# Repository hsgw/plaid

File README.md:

Plaid-C
=================

The 4x12 ortholinear keyboard kit made by through hole components only.

This is an updated version modified to use USB-C instead of Mini USB by piit79.

Atmega328p with VUSB on [QMK firmware](https://github.com/qmk/qmk_firmware).

[Build guide and bom is here](./doc)
[ビルドガイドとパーツリストはこちら](./doc)

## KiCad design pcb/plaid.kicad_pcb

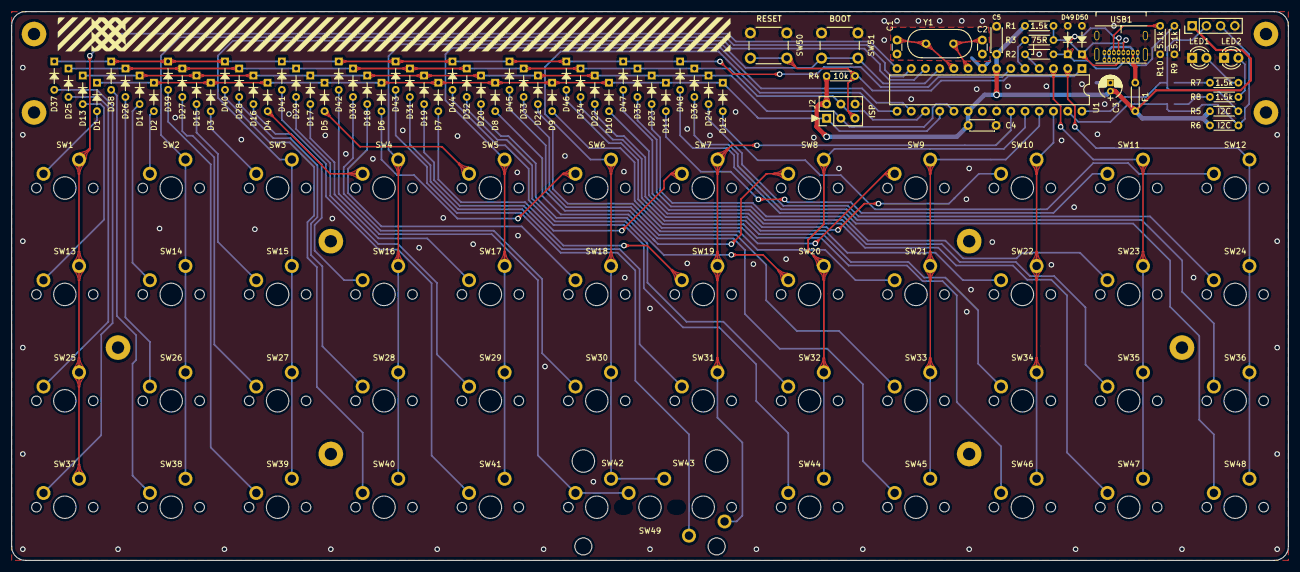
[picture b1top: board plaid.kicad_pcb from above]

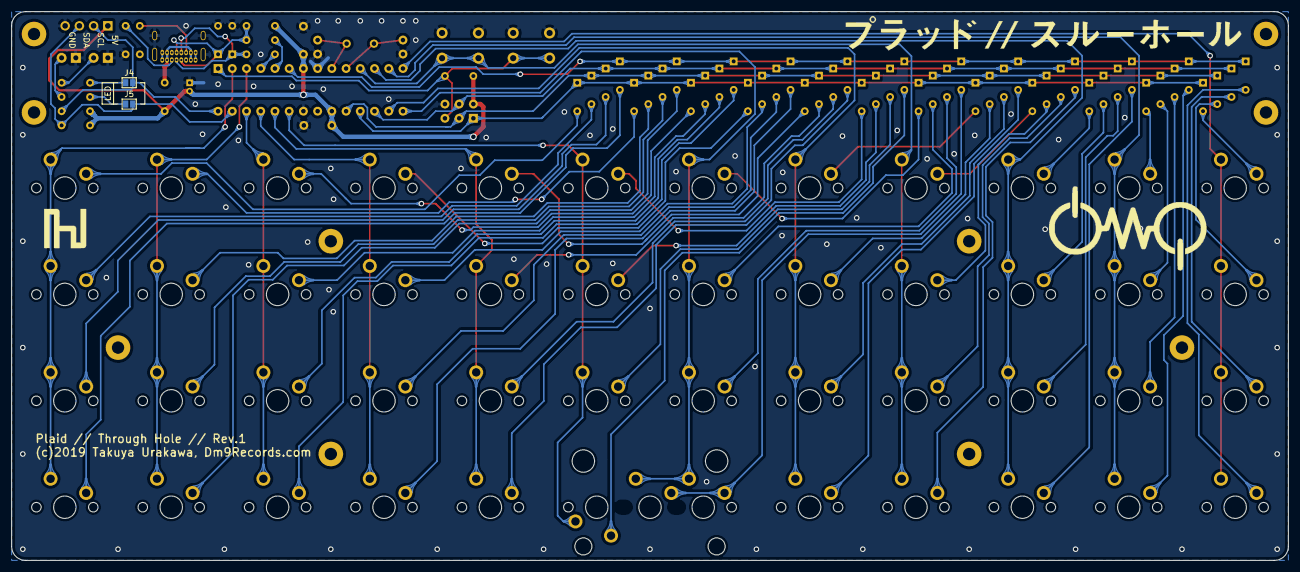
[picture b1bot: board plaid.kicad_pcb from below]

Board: 2 copper layers, 228.0 x 98.0 mm, 136 parts (2 on the bottom side), 82 nets.

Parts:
C1, C2: 20p; C_Disc_D3.0mm_W1.6mm_P2.50mm
C3: 4.7u; CP_Radial_D4.0mm_P1.50mm
C4, C5: 100n; C_Disc_D4.3mm_W1.9mm_P5.00mm
D1, D2, D3, D4, D5, D6, D7, D8, D9, D10, D11, D12, D13, D14, D15, D16, D17, D18, D19, D20, D21, D22, D23, D24, D25, D26, D27, D28, D29, D30, D31, D32, D33, D34, D35, D36, D37, D38, D39, D40, D41, D42, D43, D44, D45, D46, D47, D48: 1N4148; D_DO-35_SOD27_P5.08mm_Horizontal
D49, D50: 3.6V; D_DO-35_SOD27_P5.08mm_Horizontal
F1: 100mA; polyfuse_5.1mm
H1, H2, H3, H4, H5, H6, H7, H8, H9, H10: M2; MountingHole_2.2mm_M2_Pad
J2: AVR_ISP_6; Pin_Header_Straight_2x03_Pitch2.54mm
J3: Conn_01x04; Pin_Header_Straight_1x04_Pitch2.54mm
J4, J5: GS2
LED1: RED; LED_D3.0mm
LED2: GREEN; LED_D3.0mm
R1, R7, R8: 1.5k; R_Axial_DIN0204_L3.6mm_D1.6mm_P5.08mm_Horizontal
R2, R3: 75R; R_Axial_DIN0204_L3.6mm_D1.6mm_P5.08mm_Horizontal
R4: 10k; R_Axial_DIN0204_L3.6mm_D1.6mm_P5.08mm_Horizontal
R5, R6: I2C; R_Axial_DIN0204_L3.6mm_D1.6mm_P5.08mm_Horizontal
R9, R10: 5.1k; R_Axial_DIN0204_L3.6mm_D1.6mm_P5.08mm_Horizontal
SW1, SW2, SW3, SW4, SW5, SW6, SW7, SW8, SW9, SW10, SW11, SW12, SW13, SW14, SW15, SW16, SW17, SW18, SW19, SW20, SW21, SW22, SW23, SW24, SW25, SW26, SW27, SW28, SW29, SW30, SW31, SW32, SW33, SW34, SW35, SW36, SW37, SW38, SW39, SW40, SW41, SW42, SW43, SW44, SW45, SW46, SW47, SW48: SW_Push; SW_Cherry_MX1A_1.00u_PCB
SW49: SW_Push; SW_Cherry_MX1A_2.0U_PCB_universal_center
SW50: RESET; SW_PUSH_6mm
SW51: BOOT; SW_PUSH_6mm
U1: ATMEGA328-PU; DIP-28_W7.62mm
USB1: USB_C_GCT_USB4085-Type-C; USB_C_GCT_USB4085
Y1: 16MHz; Crystal_HC49-4H_Vertical

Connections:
+5V: C3.1, C4.1, C5.1, F1.2, J2.2, J3.1, R1.2, R4.1, R5.1, R6.1, U1.7, U1.20
/COL0: SW1.2, SW13.2, SW25.2, SW37.2, U1.14
/COL1: SW2.2, SW14.2, SW26.2, SW38.2, U1.13
/COL2: SW3.2, SW15.2, SW27.2, SW39.2, U1.12
/COL3: SW4.2, SW16.2, SW28.2, SW40.2, SW51.1, U1.11
/COL4: SW5.2, SW17.2, SW29.2, SW41.2, U1.16
/COL5: SW6.2, SW18.2, SW30.2, SW42.2, SW49.2, U1.15
/COL6: SW7.2, SW19.2, SW31.2, SW43.1, U1.23
/COL7: SW8.2, SW20.2, SW32.2, SW44.2, U1.24
/COL8: SW9.2, SW21.2, SW33.2, SW45.2, U1.25
/COL9: SW10.2, SW22.2, SW34.2, SW46.2, U1.26
/COL10: SW11.2, SW23.2, SW35.2, SW47.2, U1.3
/COL11: SW12.2, SW24.2, SW36.2, SW48.2, U1.2
/RESET: J2.5, R4.2, SW50.1, U1.1
/ROW0: D1.1, D2.1, D3.1, D4.1, D5.1, D6.1, D7.1, D8.1, D9.1, D10.1, D11.1, D12.1, J2.1, U1.18
/ROW1: D13.1, D14.1, D15.1, D16.1, D17.1, D18.1, D19.1, D20.1, D21.1, D22.1, D23.1, D24.1, J2.3, U1.19
/ROW2: D25.1, D26.1, D27.1, D28.1, D29.1, D30.1, D31.1, D32.1, D33.1, D34.1, D35.1, D36.1, J2.4, U1.17
/ROW3: D37.1, D38.1, D39.1, D40.1, D41.1, D42.1, D43.1, D44.1, D45.1, D46.1, D47.1, D48.1, U1.6
/USB_D+: R2.1, U1.4
/USB_D-: R3.1, U1.5
/i2c_SCL: J3.2, J4.2, R5.2, U1.28
/i2c_SDA: J3.3, J5.2, R6.2, U1.27
GND: C1.2, C2.2, C3.2, C4.2, C5.2, D49.2, D50.2, J2.6, J3.4, LED1.1, LED2.1, R9.1, R10.1, SW50.2, SW51.2, U1.8, U1.22, USB1.A1, USB1.A12, USB1.B1, USB1.B12, USB1.S1
unnamed: C1.1, U1.10, Y1.2
unnamed: C2.1, U1.9, Y1.1
unnamed: D1.2, SW1.1
unnamed: D2.2, SW2.1
unnamed: D3.2, SW3.1
unnamed: D4.2, SW4.1
unnamed: D5.2, SW5.1
unnamed: D6.2, SW6.1
unnamed: D7.2, SW7.1
unnamed: D8.2, SW8.1
unnamed: D9.2, SW9.1
unnamed: D10.2, SW10.1
unnamed: D11.2, SW11.1
unnamed: D12.2, SW12.1
unnamed: D13.2, SW13.1
unnamed: D14.2, SW14.1
unnamed: D15.2, SW15.1
unnamed: D16.2, SW16.1
unnamed: D17.2, SW17.1
unnamed: D18.2, SW18.1
unnamed: D19.2, SW19.1
unnamed: D20.2, SW20.1
unnamed: D21.2, SW21.1
unnamed: D22.2, SW22.1
unnamed: D23.2, SW23.1
unnamed: D24.2, SW24.1
unnamed: D25.2, SW25.1
unnamed: D26.2, SW26.1
unnamed: D27.2, SW27.1
unnamed: D28.2, SW28.1
unnamed: D29.2, SW29.1
unnamed: D30.2, SW30.1
unnamed: D31.2, SW31.1
unnamed: D32.2, SW32.1
unnamed: D33.2, SW33.1
unnamed: D34.2, SW34.1
unnamed: D35.2, SW35.1
unnamed: D36.2, SW36.1
unnamed: D37.2, SW37.1
unnamed: D38.2, SW38.1
unnamed: D39.2, SW39.1
unnamed: D40.2, SW40.1
unnamed: D41.2, SW41.1
unnamed: D42.2, SW42.1, SW49.1
unnamed: D43.2, SW43.2
unnamed: D44.2, SW44.1
unnamed: D45.2, SW45.1
unnamed: D46.2, SW46.1
unnamed: D47.2, SW47.1
unnamed: D48.2, SW48.1
unnamed: D49.1, R2.2, USB1.A6, USB1.B6
unnamed: D50.1, R1.1, R3.2, USB1.A7, USB1.B7
unnamed: F1.1, USB1.A4, USB1.A9, USB1.B4, USB1.B9
unnamed: J4.1, R7.1
unnamed: J5.1, R8.1
unnamed: LED1.2, R7.2
unnamed: LED2.2, R8.2
unnamed: R9.2, USB1.A5
unnamed: R10.2, USB1.B5

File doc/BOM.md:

# BOM 
## Included in Plaid kit
|                                   | Ref         | Qty | Value               | Description                                 |
|-----------------------------------|-------------|-----|---------------------|---------------------------------------------|
| ![22pF](./img/parts/P1020154.JPG) | C1, C2      | 2   | 22p                 | Multi layer ceramic capacitor (2.5mm pitch) |
| ![4.7uF](./img/parts/P1020157.JPG)              | C3          | 1   | 4.7u                | Electrolytic capacitor (1.5mm pitch)        |
| ![100nF](./img/parts/P1020155.JPG)              | C4, C5      | 2   | 100n                | Multi layer ceramic capacitor (5mm pitch)   |
| ![1N4148](./img/parts/P1020138.JPG)              | D1-48       | 48  | 1N4148              | General-purpose diode (DO-35)               |
| ![3.6V](./img/parts/P1020151.JPG)              | D49, D50    | 2   | 3.6V                | 3.6V Schottky diode (DO-35)                 |
| ![fuse](./img/parts/P1020156.JPG)              | F1          | 1   | 100mA               | Resettable fuse (5mm pitch)                 |
| ![USB](./img/parts/P1020147.JPG)              | J1          | 1   | USB MINI-B          | USB miniB connector                         |
| ![2x3](./img/parts/P1020158.JPG)              | J2          | 1   | 02x03               | AVR ISP pin header                          |
| ![LED](./img/parts/P1020159.JPG)              | LED1,2      | 2   | RED, GREEN              | 3mm LED                                     |
| ![1.5k](./img/parts/P1020161.JPG)              | R1, R7, R8  | 3   | 1.5k                | 1/6W resistor                               |
| ![75R](./img/parts/P1020160.JPG)              | R2, R3      | 2   | 75R                 | 1/6W resistor                               |
| ![10k](./img/parts/P1020162.JPG)              | R4          | 1   | 10k                 | 1/6W resistor                               |
| ![](./img/parts/P1020153.JPG)              | SW50, SW51     | 2   | RESET, BOOT         | 6mm tactile switch                          |
| ![](./img/parts/P1020149.JPG)              | U1          | 1   | ATMEGA328P          |                                             |
| ![](./img/parts/P1020148.JPG)              | IC Socket   | 1   | 28pin               | 28pin IC Socket                             |
| ![](./img/parts/P1020150.JPG)              | Y1          | 1   | 16MHz               |                                             |
|                                    | Screw       | 14  | M2 8mm              |                                             |
|                                    | Nut         | 26  | M2                  |                                             |
|                                    | Spacer      | 4   | M2 10mm             |                                             |
|                                    | Rubber Feet | 4   |                     |                                             |
|                                   | PCB         | 1   | MAIN PCB            |                                             |
|                                   | PCB         | 1   | BOTTOM PCB          |                                             |

## Not included
- Cherry MX compatible switches * 48   
**PCB mount (5pin) type**

- USB miniB cable

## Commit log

2018-12-12 add schematic pdf
2018-12-20 Update README.md
    fix typo
2018-12-21 add rev.alpha buildguide fix schematic
2018-12-21 fix typo
2019-01-17 add english build guide
2019-02-14 Add BOM. doesn't include switches.
    BOM has been generated through digi-key.
2019-02-17 Revert "Add BOM. doesn't include switches."
2019-02-17 Add recommend usb connector to buildguide
2019-04-07 Plaid Rev.1 Release
2019-04-07 Complete soldering.md
2019-04-08 Complete doc
2019-04-10 Add build guide in jp Fix typo
2019-04-15 Fix image of screw
2019-04-15 Add note about avr-gcc version and workaround for macOS
2019-04-15 Fix header
2019-04-16 Add note about avr-gcc version and workaround for macOS (#7)
    * Add note about avr-gcc version and workaround for macOS
    * Fix header
2019-04-18 Create LICENSE
2019-04-18 Create LICENSE (#8)
2019-04-28 note about qmk toolbox
2019-05-07 fix library name in sch
2019-12-26 Add files via upload
    reroutes the pcb avoiding the use of trace vias to increase reliabiity. boot switch and r4 are inverted 180 degrees to simplify routing but are not moved so existing aftermarket cases will still fit.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
2020-01-06 Change flash command
2020-01-16 Change flash command (#17)
    * Change flash command
    * Change flash command
2020-08-22 Update firmware.md
    make時のディレクトリの階層が変更されていると思います。
2020-08-22 update build command
2020-09-02 Replace Mini USB connector with USB-C
2020-09-02 Add gerber zip files

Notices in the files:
pcb/plaid.kicad_pcb:
(c)2019 Takuya Urakawa, Dm9Records.com
